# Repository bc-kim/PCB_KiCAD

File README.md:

# PCB design using KiCAD

1. 우선 Library 폴더를 깃에서 가져옴. 
2. SchematicLabraries는 shcematic에 대한 library를 의미함. 
3. KiCAD의 Library 폴더 위치를 설정함.
4. 설계 시작
   
# FileReposystem
1. Source
   1. Motor_MotherBoardPCB
2. Libraries
   1. BC_customs: My personal libraries
   2. Connector_Molex.pretty 
   3. Connectors_JST.pretty-master
   4. digikey-kicad-library-master
3. SchematicsLabraries
   1. MC5004P 
4. Others
   
### Project Descriptions
1. Mother_MotherBoardPCB
- 
---
1. How to manage libraries
All custom libraries are included in Libraries folder at the top. The 

2. 

Tips
* Footprint of the resisotor and capacitor should be assigned aforetime because assigning those are comfusing when lots of reisistor and capacitors are used.  
3. Reference: https://wikidocs.net/103412

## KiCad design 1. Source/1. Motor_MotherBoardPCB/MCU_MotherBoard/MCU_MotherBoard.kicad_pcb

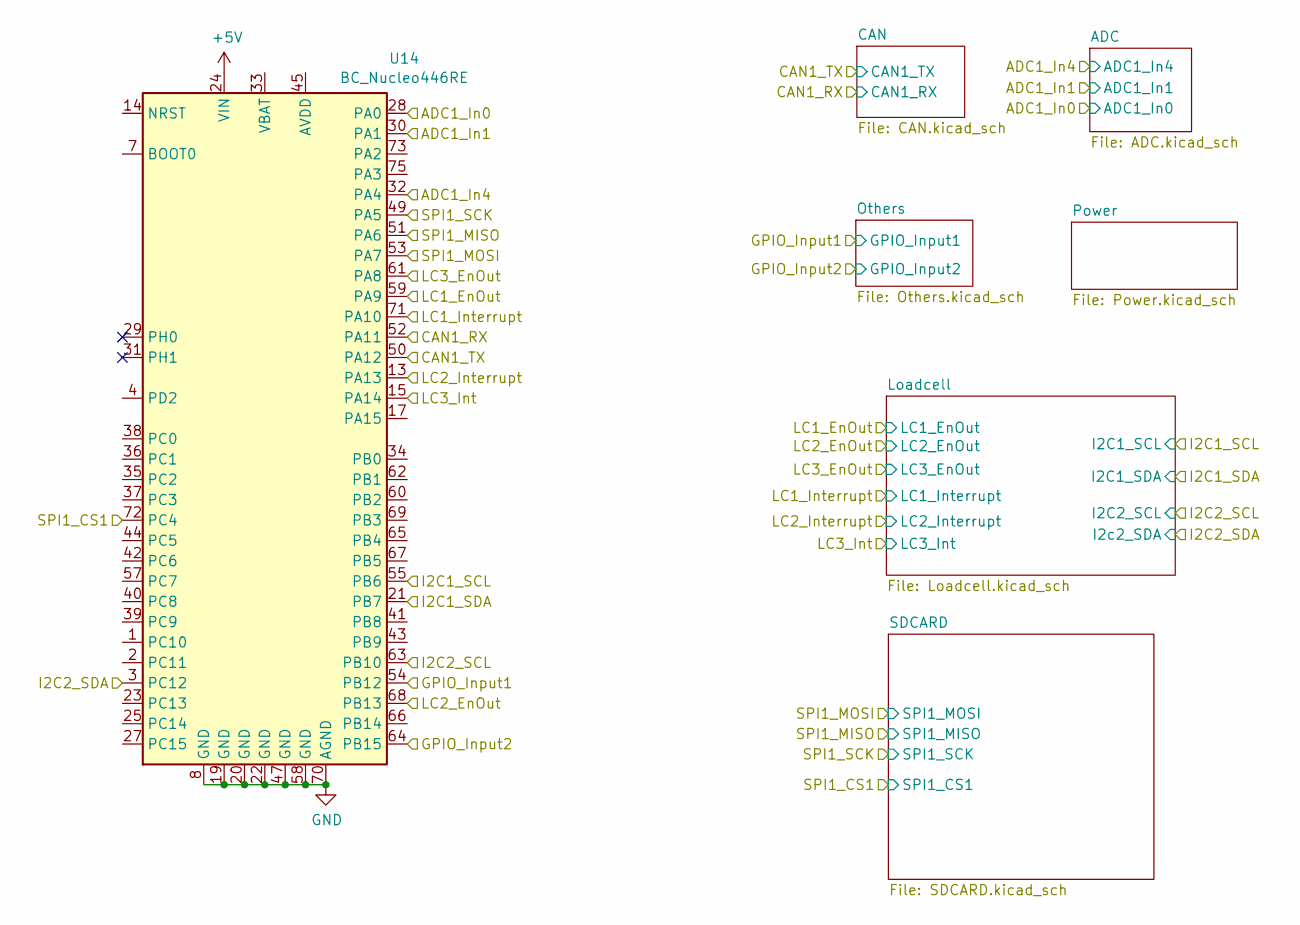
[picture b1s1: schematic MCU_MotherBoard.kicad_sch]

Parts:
U14: BC_Nucleo446RE; Main_NUCLEO-F446RE

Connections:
+5V: U14.24 (VIN); also elsewhere on the board
/ADC1_In0: U14.28 (PA0); also elsewhere on the board
/ADC1_In1: U14.30 (PA1); also elsewhere on the board
/ADC1_In4: U14.32 (PA4); also elsewhere on the board
/CAN1_RX: U14.52 (PA11); also elsewhere on the board
/CAN1_TX: U14.50 (PA12); also elsewhere on the board
/GPIO_Input1: U14.54 (PB12); also elsewhere on the board
/GPIO_Input2: U14.64 (PB15); also elsewhere on the board
/I2C1_SCL: U14.55 (PB6); also elsewhere on the board
/I2C1_SDA: U14.21 (PB7); also elsewhere on the board
/I2C2_SCL: U14.63 (PB10); also elsewhere on the board
/I2C2_SDA: U14.3 (PC12)
/LC1_EnOut: U14.59 (PA9); also elsewhere on the board
/LC1_Interrupt: U14.71 (PA10); also elsewhere on the board
/LC2_EnOut: U14.68 (PB13); also elsewhere on the board
/LC2_Interrupt: U14.13 (PA13); also elsewhere on the board
/LC3_EnOut: U14.61 (PA8); also elsewhere on the board
/LC3_Int: U14.15 (PA14); also elsewhere on the board
/SPI1_CS1: U14.72 (PC4); also elsewhere on the board
/SPI1_MISO: U14.51 (PA6); also elsewhere on the board
/SPI1_MOSI: U14.53 (PA7); also elsewhere on the board
/SPI1_SCK: U14.49 (PA5); also elsewhere on the board
GND: U14.8 (GND), U14.19 (GND), U14.20 (GND), U14.22 (GND), U14.47 (GND), U14.58 (GND), U14.70 (AGND); also elsewhere on the board

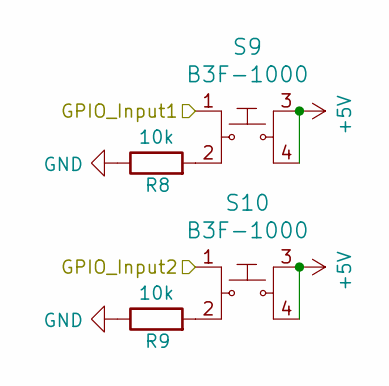
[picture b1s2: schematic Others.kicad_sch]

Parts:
R8, R9: 10k; R_Axial_DIN0204_L3.6mm_D1.6mm_P2.54mm_Vertical
S9, S10: B3F-1000; Switch_Tactile_THT_B3F-1xxx; MPN B3F-1000; Digi-Key_PN SW400-ND

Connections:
+5V: S9.3, S9.4, S10.3, S10.4; also elsewhere on the board
/GPIO_Input1: S9.1; also elsewhere on the board
/GPIO_Input2: S10.1; also elsewhere on the board
GND: R8.1, R9.1; also elsewhere on the board
unnamed: R8.2, S9.2
unnamed: R9.2, S10.2

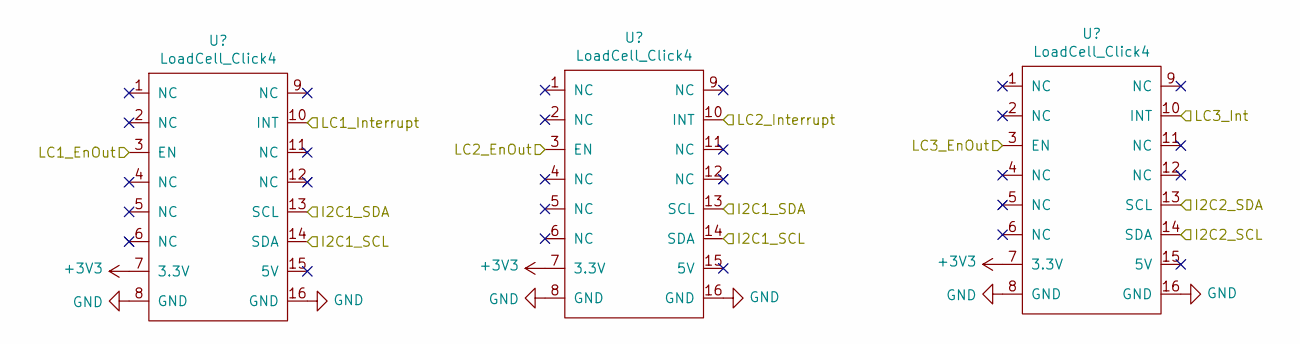
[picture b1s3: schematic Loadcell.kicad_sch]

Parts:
U15, U16, U17: LoadCell_Click4

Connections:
+3V3: U15.7 (3.3V), U16.7 (3.3V), U17.7 (3.3V); also elsewhere on the board
/I2C1_SCL: U15.14 (SDA), U16.14 (SDA); also elsewhere on the board
/I2C1_SDA: U15.13 (SCL), U16.13 (SCL); also elsewhere on the board
/I2C2_SCL: U17.14 (SDA); also elsewhere on the board
/LC1_EnOut: U15.3 (EN); also elsewhere on the board
/LC1_Interrupt: U15.10 (INT); also elsewhere on the board
/LC2_EnOut: U16.3 (EN); also elsewhere on the board
/LC2_Interrupt: U16.10 (INT); also elsewhere on the board
/LC3_EnOut: U17.3 (EN); also elsewhere on the board
/LC3_Int: U17.10 (INT); also elsewhere on the board
/Loadcell/I2C2_SDA: U17.13 (SCL)
GND: U15.8 (GND), U15.16 (GND), U16.8 (GND), U16.16 (GND), U17.8 (GND), U17.16 (GND); also elsewhere on the board

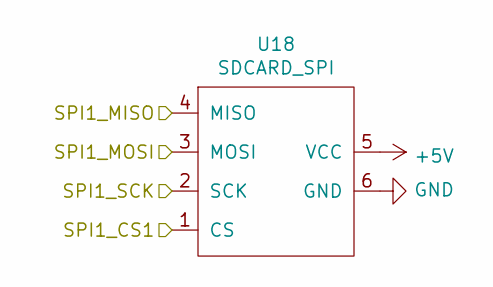
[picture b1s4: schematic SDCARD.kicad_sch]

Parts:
U18: SDCARD_SPI

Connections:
+5V: U18.5 (VCC); also elsewhere on the board
/SPI1_CS1: U18.1 (CS); also elsewhere on the board
/SPI1_MISO: U18.4 (MISO); also elsewhere on the board
/SPI1_MOSI: U18.3 (MOSI); also elsewhere on the board
/SPI1_SCK: U18.2 (SCK); also elsewhere on the board
GND: U18.6 (GND); also elsewhere on the board

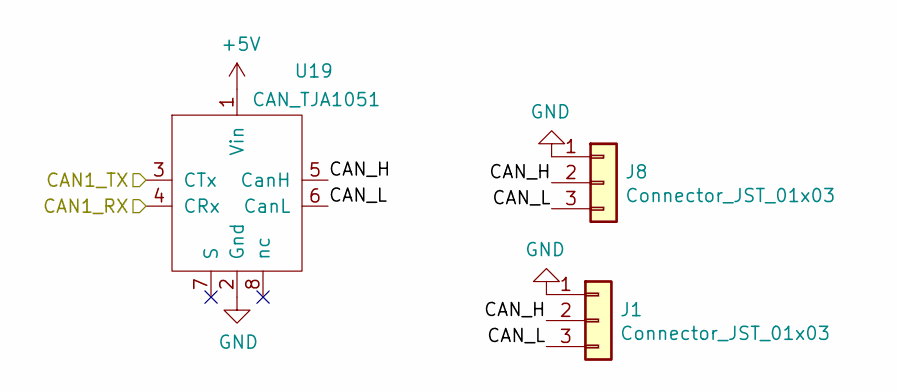
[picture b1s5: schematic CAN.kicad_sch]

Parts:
J1, J8: Connector_JST_01x03; JST_XH_S03B-XH-A_03x2.50mm_Angled
U19: CAN_TJA1051

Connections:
+5V: U19.1 (Vin); also elsewhere on the board
/CAN1_RX: U19.4 (CRx); also elsewhere on the board
/CAN1_TX: U19.3 (CTx); also elsewhere on the board
/CAN/CAN_H: J1.2, J8.2, U19.5 (CanH)
/CAN/CAN_L: J1.3, J8.3, U19.6 (CanL)
GND: J1.1, J8.1, U19.2 (Gnd); also elsewhere on the board

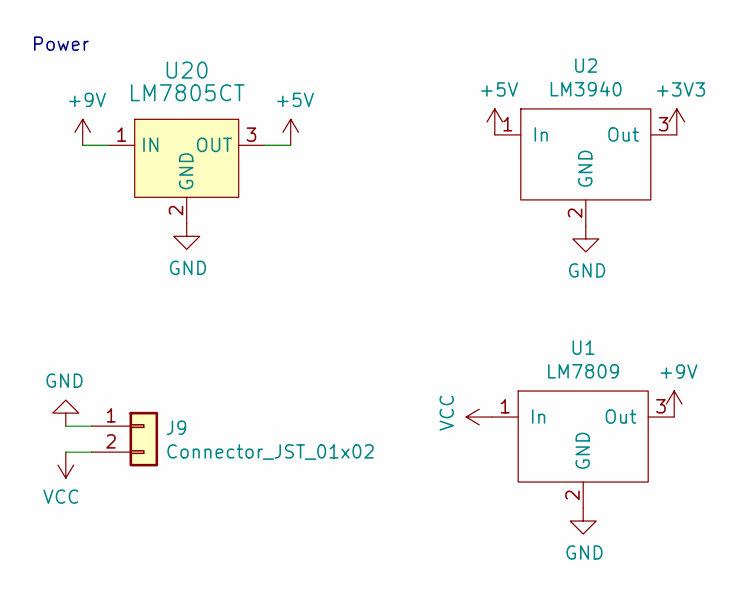
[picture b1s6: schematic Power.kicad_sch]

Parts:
J9: Connector_JST_01x02; JST_XH_S02B-XH-A_02x2.50mm_Angled
U1: LM7809; TO-220-3
U2: LM3940; TO-220-3
U20: LM7805CT; TO-220-3; MPN LM7805CT; Digi-Key_PN LM7805CT-ND

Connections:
+3V3: U2.3 (Out); also elsewhere on the board
+5V: U2.1 (In), U20.3 (OUT); also elsewhere on the board
+9V: U1.3 (Out), U20.1 (IN); also elsewhere on the board
GND: J9.1, U1.2 (GND), U2.2 (GND), U20.2 (GND); also elsewhere on the board
VCC: J9.2, U1.1 (In)

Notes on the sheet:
Power

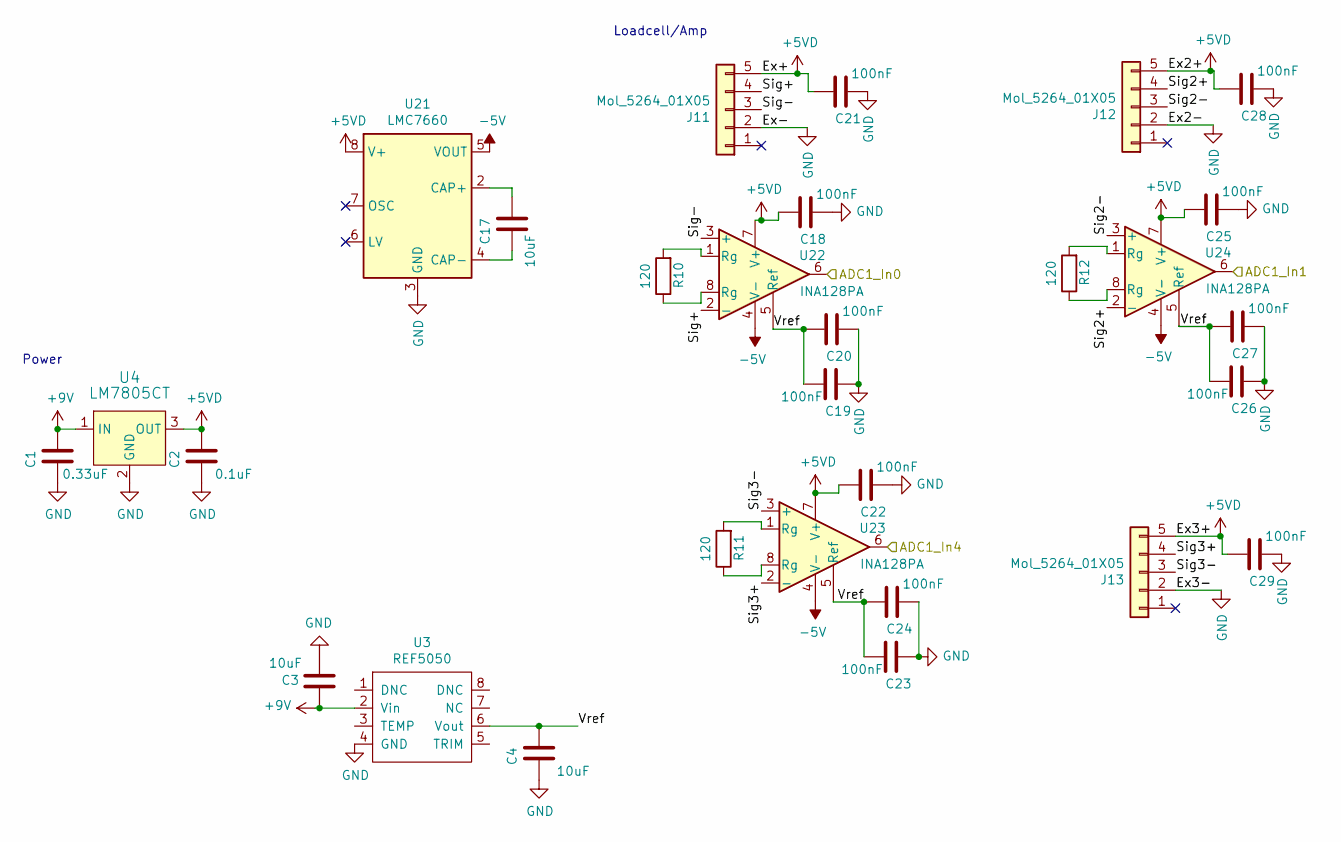
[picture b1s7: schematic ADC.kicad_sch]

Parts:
C1: 0.33uF; CP_Radial_D8.0mm_P3.50mm
C2: 0.1uF; C_Disc_D4.7mm_W2.5mm_P5.00mm
C3, C4: 10uF; CP_EIA-7343-31_Kemet-D
C17: 10uF; CP_Radial_D8.0mm_P3.50mm
C18, C19, C20, C21, C22, C23, C24, C25, C26, C27, C28, C29: 100nF; C_Disc_D4.7mm_W2.5mm_P5.00mm
J11, J12, J13: Mol_5264_01X05; Molex_KK-254_AE-6410-05A_1x05_P2.54mm_Vertical
R10, R11, R12: 120; R_Axial_DIN0204_L3.6mm_D1.6mm_P2.54mm_Vertical
U3: REF5050
U4: LM7805CT; TO-220-3; MPN LM7805CT; Digi-Key_PN LM7805CT-ND
U21: LMC7660; LMC7660_THT
U22, U23, U24: INA128PA

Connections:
+5VD: C2.2, C18.2, C21.2, C22.2, C25.2, C28.2, C29.2, J11.5, J12.5, J13.5, U4.3 (OUT), U21.8 (V+), U22.7 (V+), U23.7 (V+), U24.7 (V+)
+9V: C1.2, C3.2, U3.2 (Vin), U4.1 (IN); also elsewhere on the board
-5V: U21.5 (VOUT), U22.4 (V-), U23.4 (V-), U24.4 (V-)
/ADC1_In0: U22.6; also elsewhere on the board
/ADC1_In1: U24.6; also elsewhere on the board
/ADC1_In4: U23.6; also elsewhere on the board
/ADC/Sig2+: J12.4, U24.2 (-)
/ADC/Sig2-: J12.3, U24.3 (+)
/ADC/Sig3+: J13.4, U23.2 (-)
/ADC/Sig3-: J13.3, U23.3 (+)
/ADC/Sig+: J11.4, U22.2 (-)
/ADC/Sig-: J11.3, U22.3 (+)
/ADC/Vref: C4.2, C19.2, C20.2, C23.2, C24.2, C26.2, C27.2, U3.6 (Vout), U22.5 (Ref), U23.5 (Ref), U24.5 (Ref)
GND: C1.1, C2.1, C3.1, C4.1, C18.1, C19.1, C20.1, C21.1, C22.1, C23.1, C24.1, C25.1, C26.1, C27.1, C28.1, C29.1, J11.2, J12.2, J13.2, U3.4 (GND), U4.2 (GND), U21.3 (GND); also elsewhere on the board
unnamed: C17.1, U21.4 (CAP-)
unnamed: C17.2, U21.2 (CAP+)
unnamed: R10.1, U22.8 (Rg)
unnamed: R10.2, U22.1 (Rg)
unnamed: R11.1, U23.8 (Rg)
unnamed: R11.2, U23.1 (Rg)
unnamed: R12.1, U24.8 (Rg)
unnamed: R12.2, U24.1 (Rg)

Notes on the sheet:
Loadcell/Amp
Power

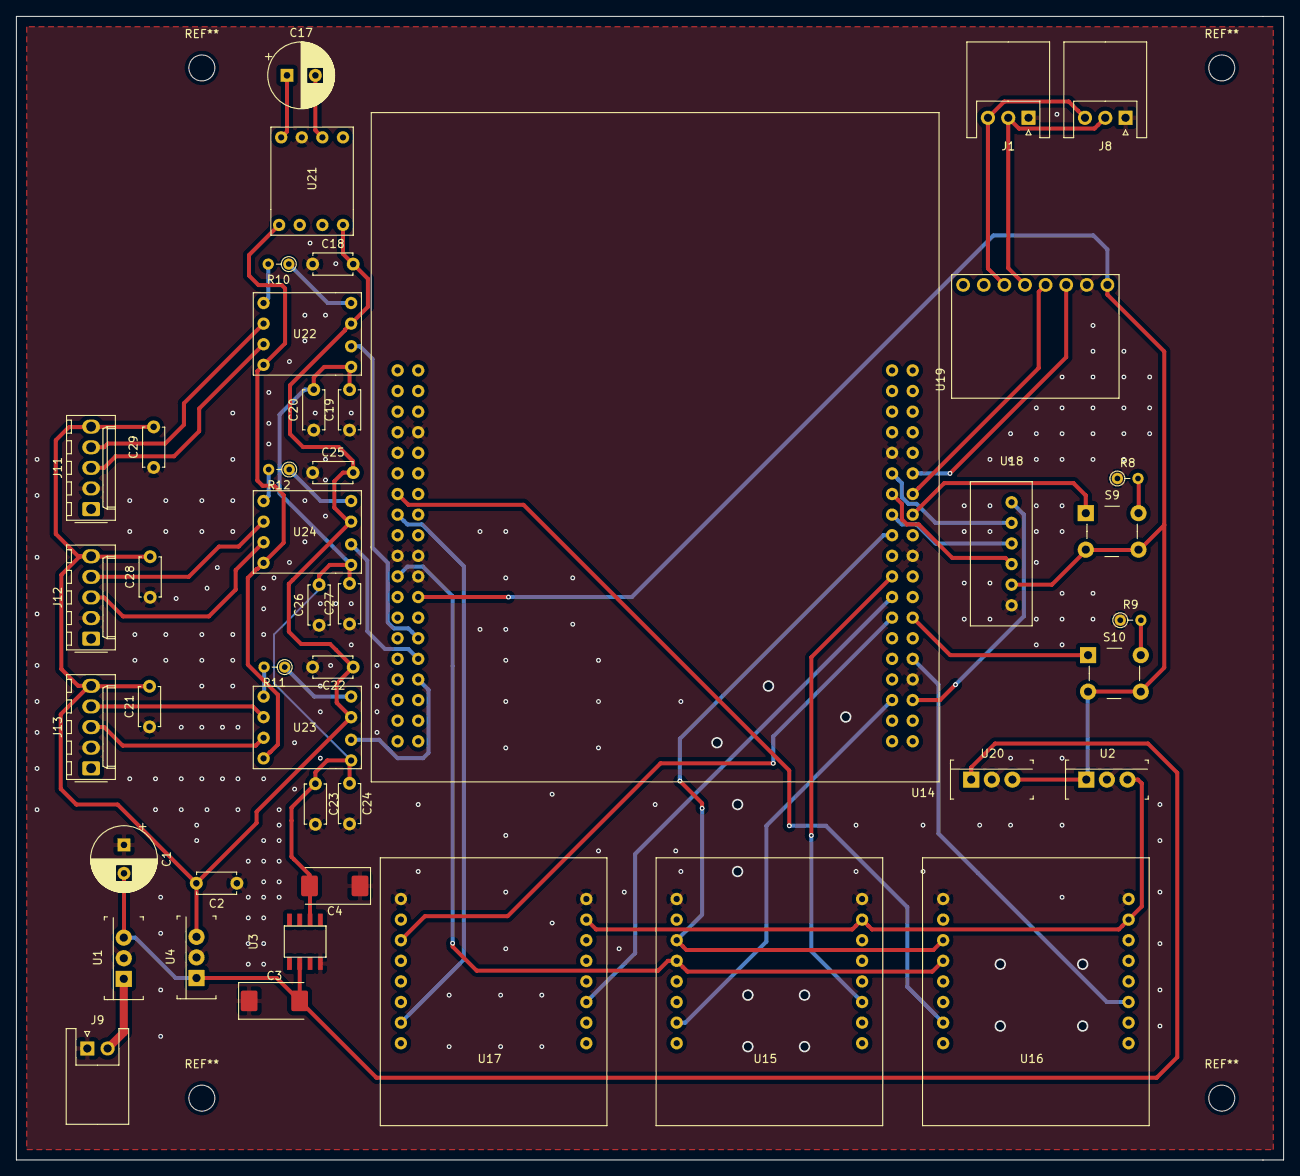
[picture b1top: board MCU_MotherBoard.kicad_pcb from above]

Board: 2 copper layers, 156.2 x 141.0 mm, 45 parts (0 on the bottom side), 46 nets.

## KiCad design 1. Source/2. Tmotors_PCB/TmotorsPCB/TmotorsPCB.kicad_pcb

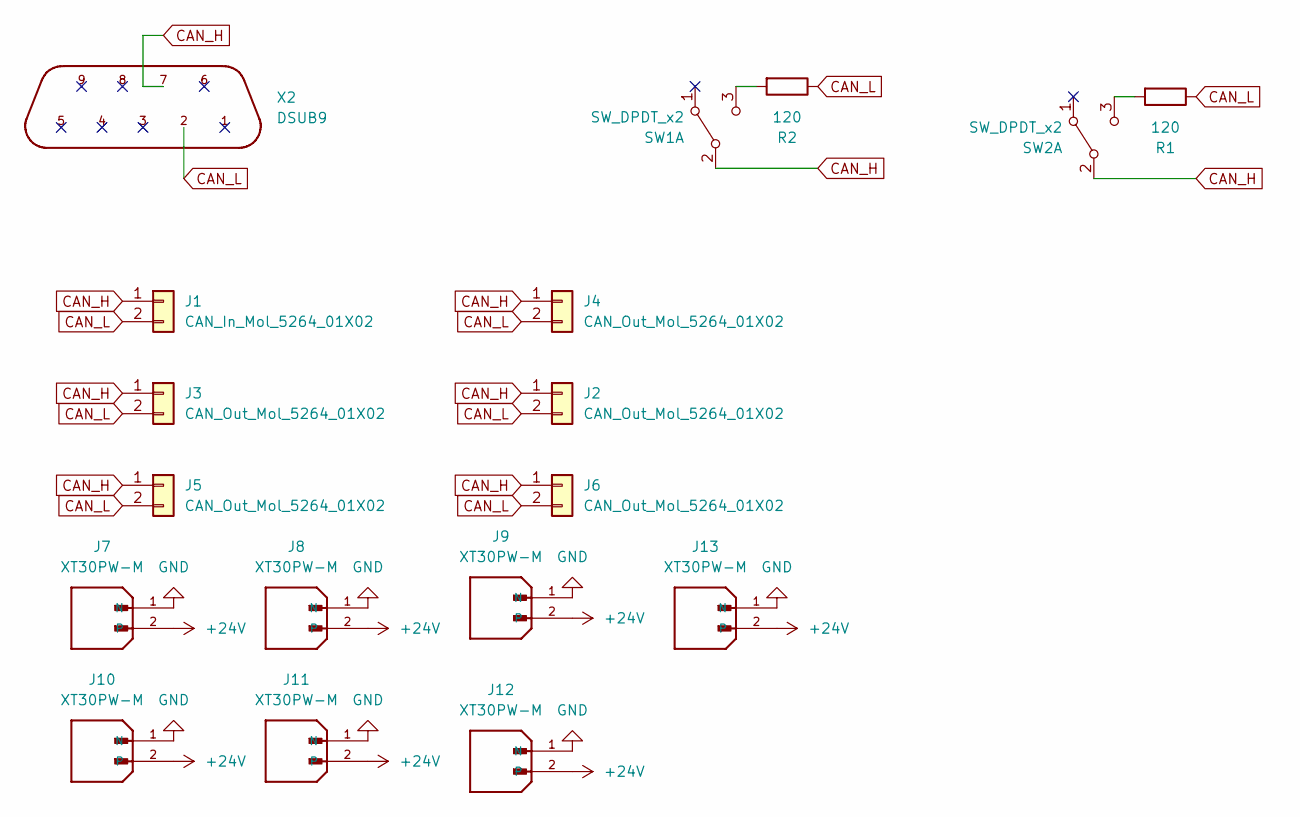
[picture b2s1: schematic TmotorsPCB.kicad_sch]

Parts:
J1: CAN_In_Mol_5264_01X02; Molex_PicoBlade_53047-0210_1x02_P1.25mm_Vertical
J2, J3, J4, J5, J6: CAN_Out_Mol_5264_01X02; Molex_PicoBlade_53047-0210_1x02_P1.25mm_Vertical
J7, J8, J9, J10, J11, J12, J13: XT30PW-M; AMASS_XT30PW-F_1x02_P2.50mm_Horizontal; PARTREV 1.2
R1, R2: 120; R_Axial_DIN0207_L6.3mm_D2.5mm_P7.62mm_Horizontal
SW1, SW2: SW_DPDT_x2; SW_slide-03
X2: DSUB9; DSUB-9_Female_Horizontal_P2.77x2.84mm_EdgePinOffset14.56mm_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

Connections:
+24V: J7.2, J8.2, J9.2, J10.2, J11.2, J12.2, J13.2
CAN_H: J1.1, J2.1, J3.1, J4.1, J5.1, J6.1, SW1.2 (B), SW2.2 (B), X2.7
CAN_L: J1.2, J2.2, J3.2, J4.2, J5.2, J6.2, R1.1, R2.1, X2.2
GND: J7.1 (N), J8.1 (N), J9.1 (N), J10.1 (N), J11.1 (N), J12.1 (N), J13.1 (N)
unnamed: R2.2, SW1.3 (C)
unnamed: R1.2, SW2.3 (C)

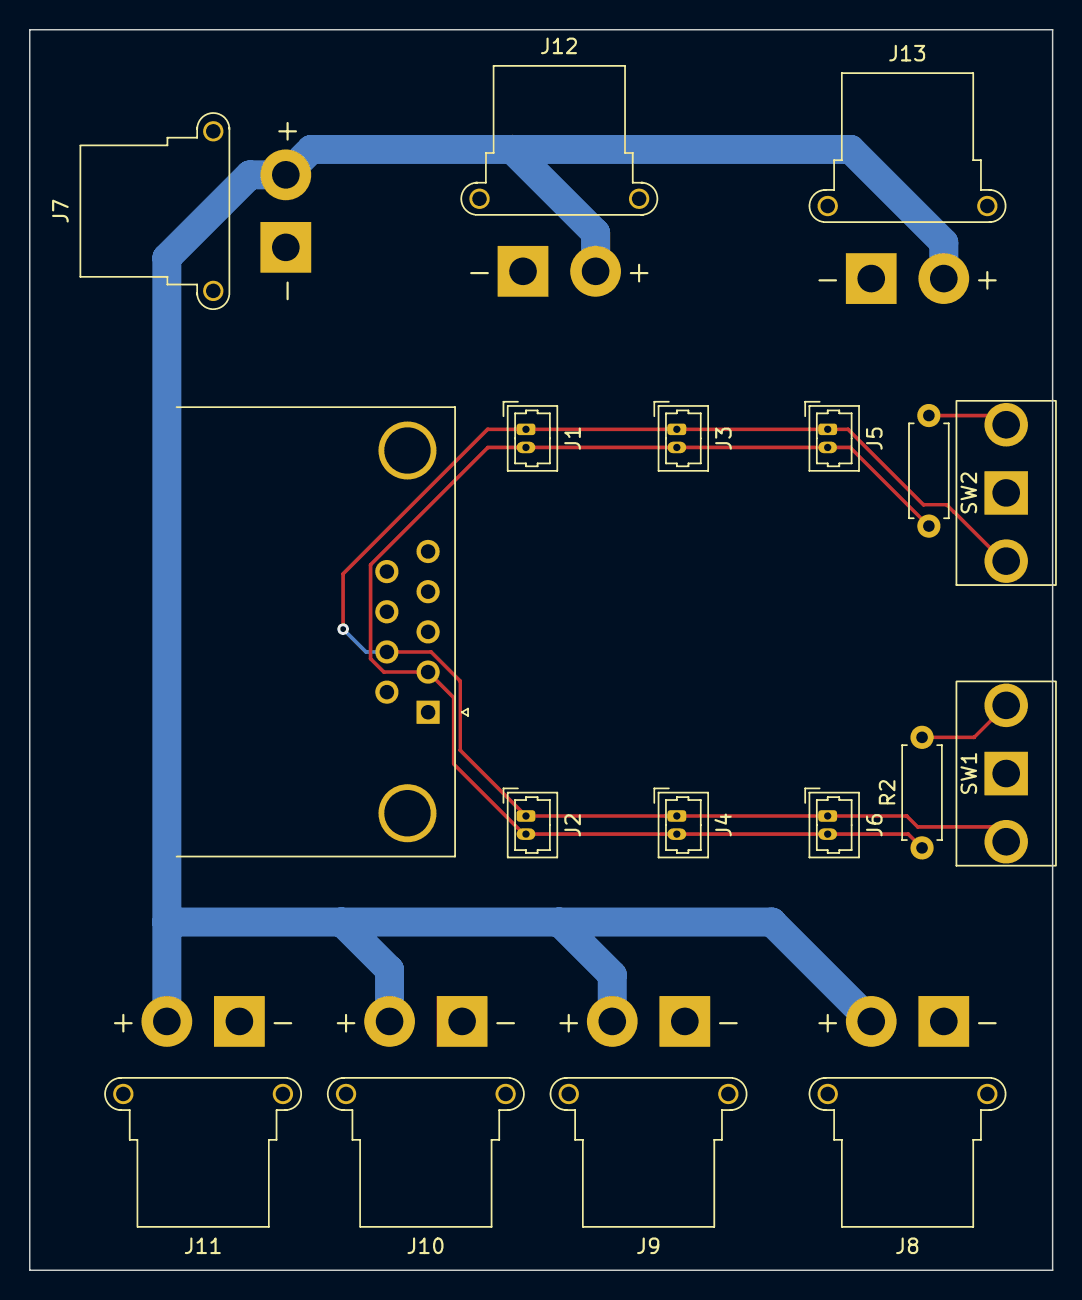
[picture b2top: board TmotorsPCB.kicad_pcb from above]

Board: 2 copper layers, 70.5 x 85.5 mm, 18 parts (0 on the bottom side), 6 nets.

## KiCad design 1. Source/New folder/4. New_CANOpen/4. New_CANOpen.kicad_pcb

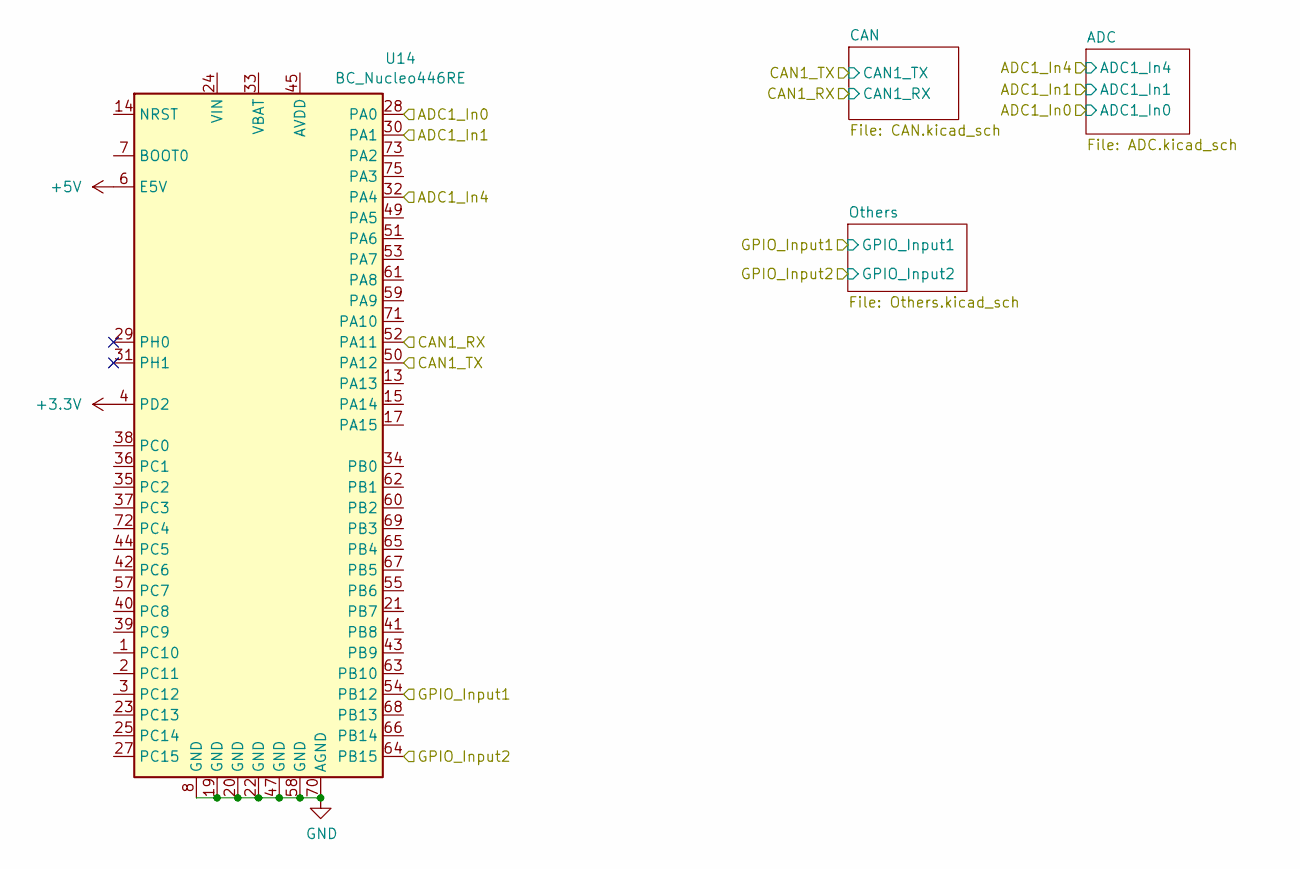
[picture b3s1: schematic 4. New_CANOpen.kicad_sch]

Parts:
U14: BC_Nucleo446RE; Main_NUCLEO-F446RE

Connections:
+3.3V: U14.4 (PD2); also elsewhere on the board
+5V: U14.6 (E5V); also elsewhere on the board
/ADC1_In0: U14.28 (PA0); also elsewhere on the board
/ADC1_In1: U14.30 (PA1); also elsewhere on the board
/ADC1_In4: U14.32 (PA4); also elsewhere on the board
/CAN1_RX: U14.52 (PA11); also elsewhere on the board
/CAN1_TX: U14.50 (PA12); also elsewhere on the board
/GPIO_Input1: U14.54 (PB12); also elsewhere on the board
/GPIO_Input2: U14.64 (PB15); also elsewhere on the board
GND: U14.8 (GND), U14.19 (GND), U14.20 (GND), U14.22 (GND), U14.47 (GND), U14.58 (GND), U14.70 (AGND); also elsewhere on the board

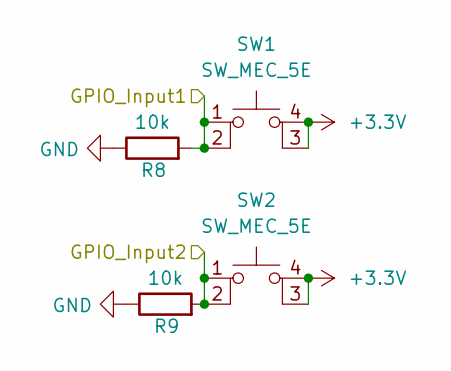
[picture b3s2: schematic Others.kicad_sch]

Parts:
R8, R9: 10k; R_Axial_DIN0411_L9.9mm_D3.6mm_P15.24mm_Horizontal
SW1, SW2: SW_MEC_5E; SW_B3F-1000_OMR

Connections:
+3.3V: SW1.3 (K), SW1.4 (A), SW2.3 (K), SW2.4 (A); also elsewhere on the board
/GPIO_Input1: R8.2, SW1.1, SW1.2; also elsewhere on the board
/GPIO_Input2: R9.2, SW2.1, SW2.2; also elsewhere on the board
GND: R8.1, R9.1; also elsewhere on the board

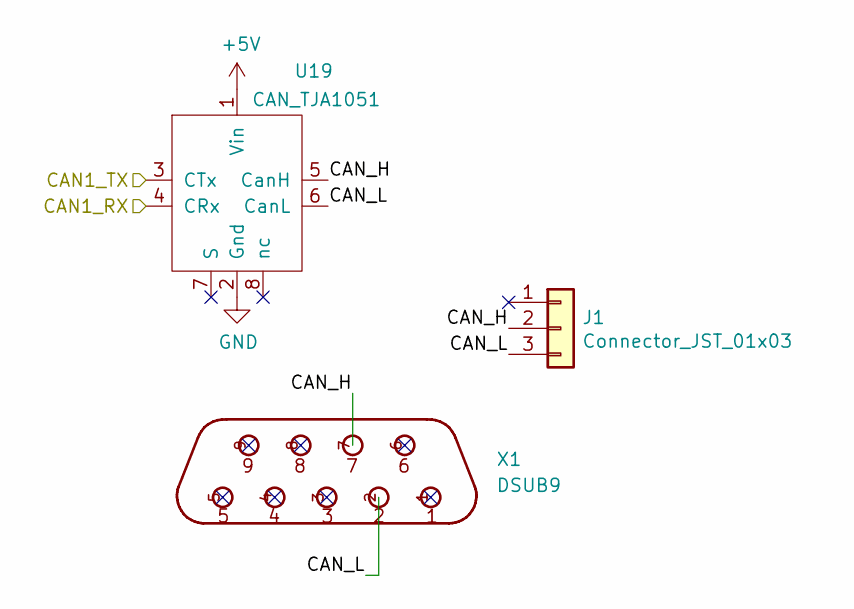
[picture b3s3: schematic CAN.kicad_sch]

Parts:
J1: Connector_JST_01x03; JST_XH_S3B-XH-A-1_1x03_P2.50mm_Horizontal
U19: CAN_TJA1051
X1: DSUB9; DSUB-9_Female_Horizontal_P2.77x2.84mm_EdgePinOffset7.70mm_H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

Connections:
+5V: U19.1 (Vin); also elsewhere on the board
/CAN1_RX: U19.4 (CRx); also elsewhere on the board
/CAN1_TX: U19.3 (CTx); also elsewhere on the board
/CAN/CAN_H: J1.2, U19.5 (CanH), X1.7
/CAN/CAN_L: J1.3, U19.6 (CanL), X1.2
GND: U19.2 (Gnd); also elsewhere on the board

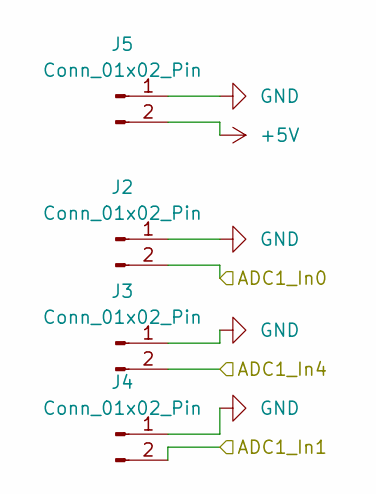
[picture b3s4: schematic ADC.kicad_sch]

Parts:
J2, J3, J4, J5: Conn_01x02_Pin; CON_436500227_MOL

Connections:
+5V: J5.2; also elsewhere on the board
/ADC1_In0: J2.2; also elsewhere on the board
/ADC1_In1: J4.2; also elsewhere on the board
/ADC1_In4: J3.2; also elsewhere on the board
GND: J2.1, J3.1, J4.1, J5.1; also elsewhere on the board

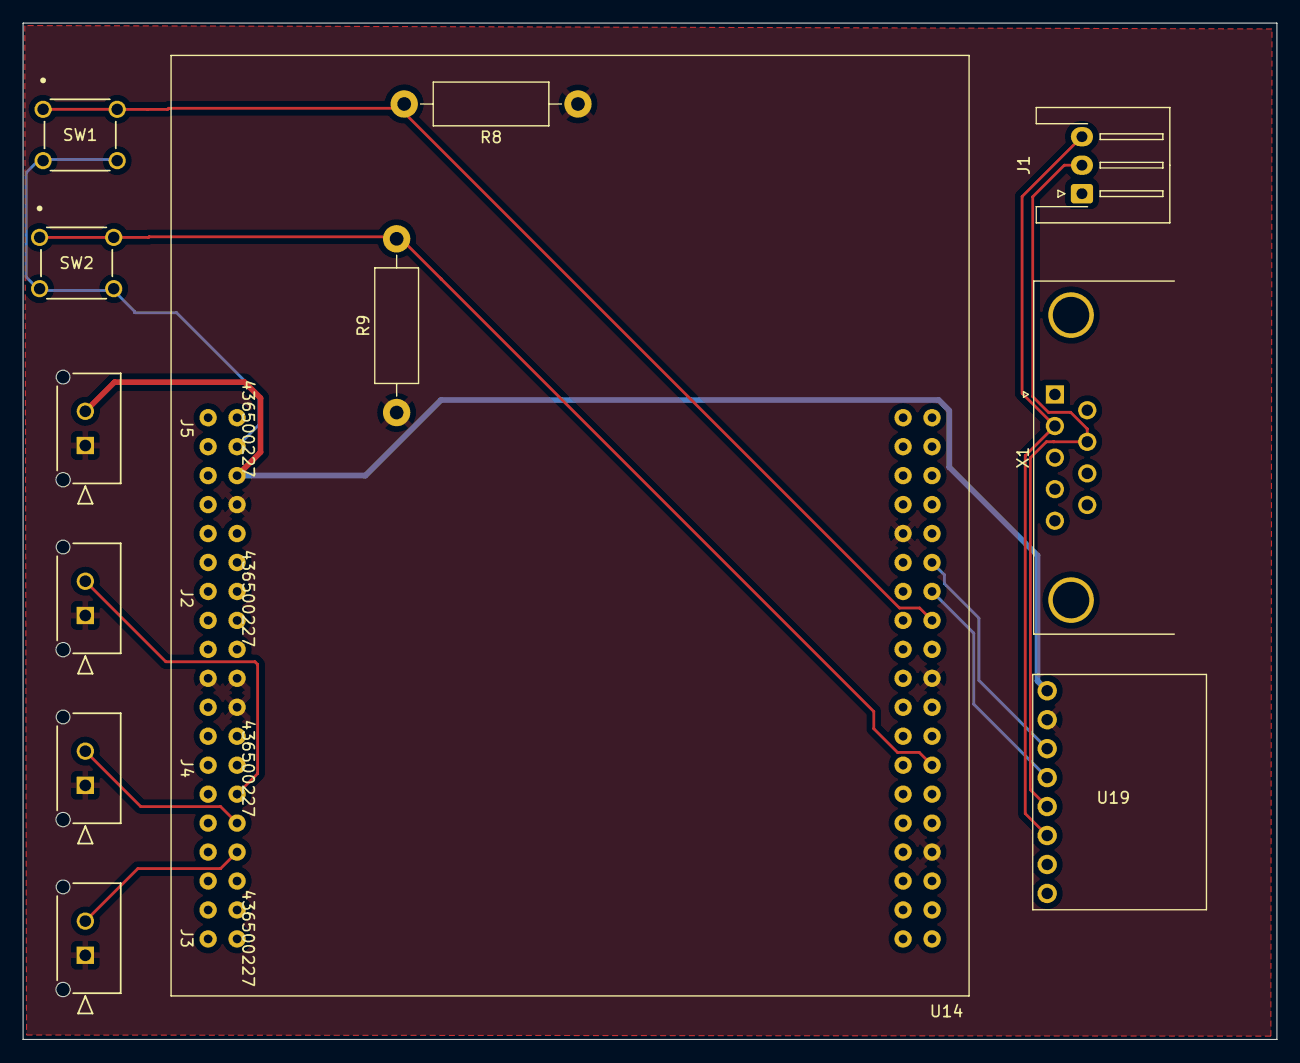
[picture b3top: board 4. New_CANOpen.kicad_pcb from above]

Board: 2 copper layers, 110.0 x 89.2 mm, 12 parts (0 on the bottom side), 12 nets.

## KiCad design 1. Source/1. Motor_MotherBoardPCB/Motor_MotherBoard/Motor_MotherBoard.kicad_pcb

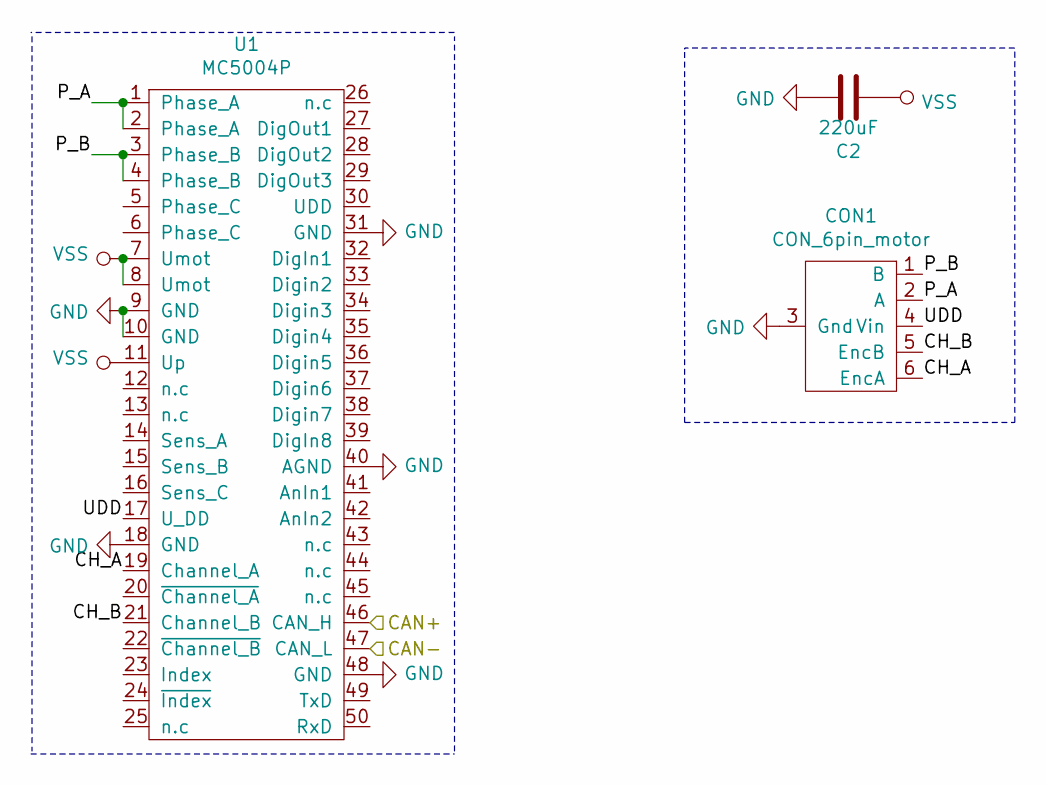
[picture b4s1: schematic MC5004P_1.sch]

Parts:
C2: 220uF; CP_Radial_D8.0mm_P3.50mm
CON1: CON_6pin_motor; IDC-Header_2x03_P2.54mm_Vertical
U1: MC5004P

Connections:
/CAN+: U1.46 (CAN_H); also elsewhere on the board
/CAN-: U1.47 (CAN_L); also elsewhere on the board
/MC5004P_1/CH_A: CON1.6 (EncA), U1.19 (Channel_A)
/MC5004P_1/CH_B: CON1.5 (EncB), U1.21 (Channel_B)
/MC5004P_1/P_A: CON1.2 (A), U1.1 (Phase_A), U1.2 (Phase_A)
/MC5004P_1/P_B: CON1.1 (B), U1.3 (Phase_B), U1.4 (Phase_B)
/MC5004P_1/UDD: CON1.4 (Vin), U1.17 (U_DD)
GND: C2.1, CON1.3 (Gnd), U1.9 (GND), U1.10 (GND), U1.18 (GND), U1.31 (GND), U1.40 (AGND), U1.48 (GND); also elsewhere on the board
VSS: C2.2, U1.7 (Umot), U1.8 (Umot), U1.11 (Up); also elsewhere on the board

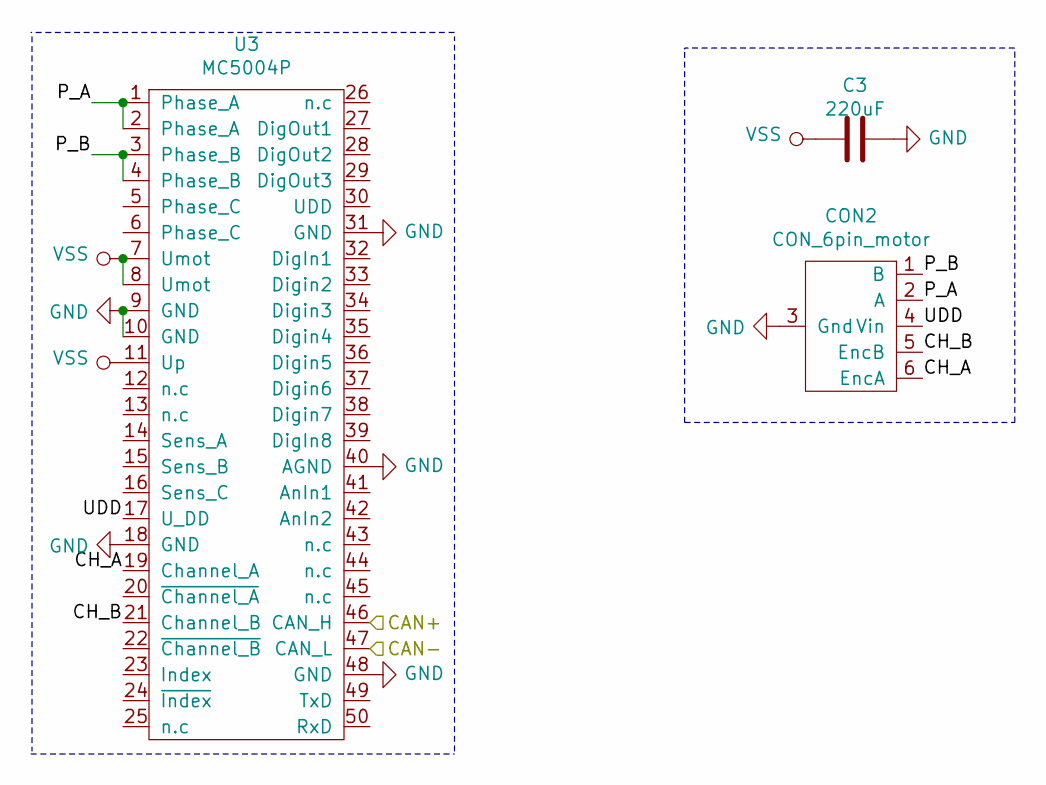
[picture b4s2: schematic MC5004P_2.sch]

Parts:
C3: 220uF; CP_Radial_D8.0mm_P3.80mm
CON2: CON_6pin_motor; IDC-Header_2x03_P2.54mm_Vertical
U3: MC5004P

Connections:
/CAN+: U3.46 (CAN_H); also elsewhere on the board
/CAN-: U3.47 (CAN_L); also elsewhere on the board
/MC5004P_2/CH_A: CON2.6 (EncA), U3.19 (Channel_A)
/MC5004P_2/CH_B: CON2.5 (EncB), U3.21 (Channel_B)
/MC5004P_2/P_A: CON2.2 (A), U3.1 (Phase_A), U3.2 (Phase_A)
/MC5004P_2/P_B: CON2.1 (B), U3.3 (Phase_B), U3.4 (Phase_B)
/MC5004P_2/UDD: CON2.4 (Vin), U3.17 (U_DD)
GND: C3.1, CON2.3 (Gnd), U3.9 (GND), U3.10 (GND), U3.18 (GND), U3.31 (GND), U3.40 (AGND), U3.48 (GND); also elsewhere on the board
VSS: C3.2, U3.7 (Umot), U3.8 (Umot), U3.11 (Up); also elsewhere on the board

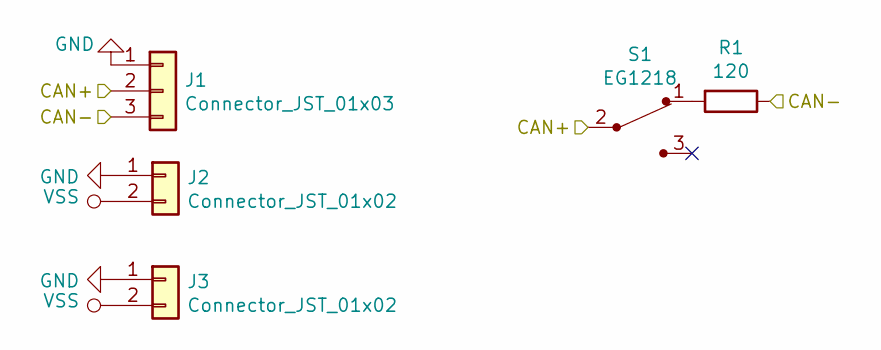
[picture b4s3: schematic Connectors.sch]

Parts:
J1: Connector_JST_01x03; JST_XH_S03B-XH-A_03x2.50mm_Angled
J2, J3: Connector_JST_01x02; JST_XH_S02B-XH-A_02x2.50mm_Angled
R1: 120; R_Axial_DIN0204_L3.6mm_D1.6mm_P7.62mm_Horizontal
S1: EG1218; Switch_Slide_11.6x4mm_EG1218; MPN EG1218; Digi-Key_PN EG1903-ND

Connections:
/CAN+: J1.2, S1.2; also elsewhere on the board
/CAN-: J1.3, R1.1; also elsewhere on the board
GND: J1.1, J2.1, J3.1; also elsewhere on the board
unnamed: R1.2, S1.1
VSS: J2.2, J3.2; also elsewhere on the board

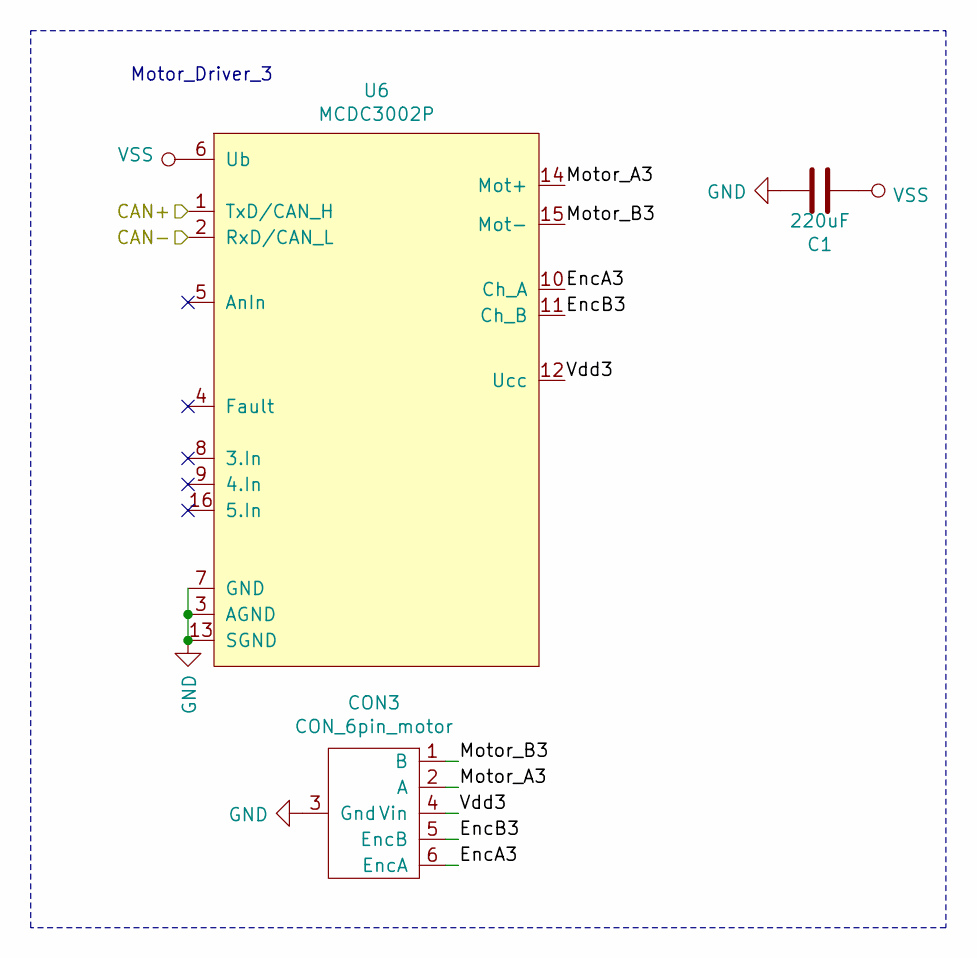
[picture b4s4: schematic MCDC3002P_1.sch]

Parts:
C1: 220uF; CP_Radial_D8.0mm_P3.50mm
CON3: CON_6pin_motor; IDC-Header_2x03_P2.54mm_Vertical
U6: MCDC3002P; MCDC_3002P

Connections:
/CAN+: U6.1 (TxD/CAN_H); also elsewhere on the board
/CAN-: U6.2 (RxD/CAN_L); also elsewhere on the board
/MCDC3002P_1/EncA3: CON3.6 (EncA), U6.10 (Ch_A)
/MCDC3002P_1/EncB3: CON3.5 (EncB), U6.11 (Ch_B)
/MCDC3002P_1/Motor_A3: CON3.2 (A), U6.14 (Mot+)
/MCDC3002P_1/Motor_B3: CON3.1 (B), U6.15 (Mot-)
/MCDC3002P_1/Vdd3: CON3.4 (Vin), U6.12 (Ucc)
GND: C1.1, CON3.3 (Gnd), U6.3 (AGND), U6.7 (GND), U6.13 (SGND); also elsewhere on the board
VSS: C1.2, U6.6 (Ub); also elsewhere on the board

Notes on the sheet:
Motor_Driver_3

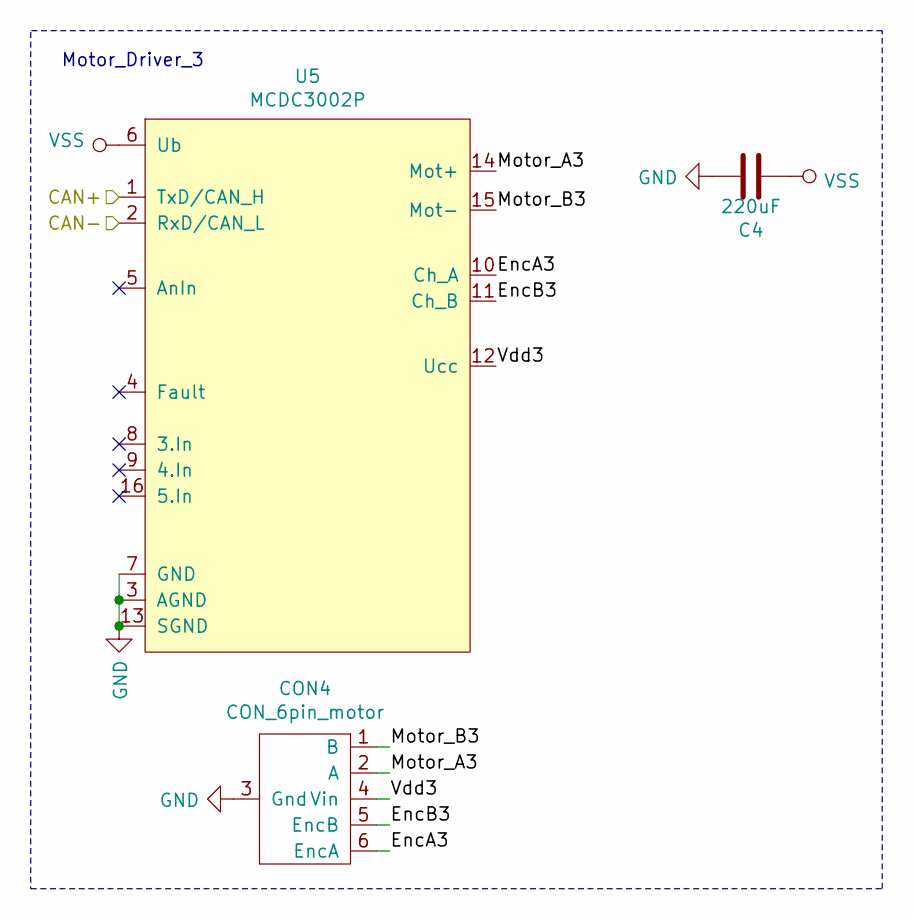
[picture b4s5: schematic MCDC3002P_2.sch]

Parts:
C4: 220uF; CP_Radial_D8.0mm_P3.50mm
CON4: CON_6pin_motor; IDC-Header_2x03_P2.54mm_Vertical
U5: MCDC3002P; MCDC_3002P

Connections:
/CAN+: U5.1 (TxD/CAN_H); also elsewhere on the board
/CAN-: U5.2 (RxD/CAN_L); also elsewhere on the board
/MCDC3002P_2/EncA3: CON4.6 (EncA), U5.10 (Ch_A)
/MCDC3002P_2/EncB3: CON4.5 (EncB), U5.11 (Ch_B)
/MCDC3002P_2/Motor_A3: CON4.2 (A), U5.14 (Mot+)
/MCDC3002P_2/Motor_B3: CON4.1 (B), U5.15 (Mot-)
/MCDC3002P_2/Vdd3: CON4.4 (Vin), U5.12 (Ucc)
GND: C4.1, CON4.3 (Gnd), U5.3 (AGND), U5.7 (GND), U5.13 (SGND); also elsewhere on the board
VSS: C4.2, U5.6 (Ub); also elsewhere on the board

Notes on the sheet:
Motor_Driver_3
